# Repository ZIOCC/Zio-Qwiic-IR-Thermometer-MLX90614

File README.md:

# Zio Qwiic Surface IR Thermometer (MLX90614)

> This product can be available for purchase [here](https://www.smart-prototyping.com/Zio-Qwiic-Surface-Temperature-Infrared-Sensor-MLX9061).

##### Description

The latest incorporation to our Qwiic family is this high precision temperature module!  It has a very cool feature on sensing temperatures remotely thanks to the infrared light emitted. Most of the object temperature sensors need to be in contact to the object to take a measurement, but the ZIO IR Thermometer determines the light rebounding off objects, in this way the temperature can be sensed even if the object is located in a certain distance. To get a temperature measurement just point the sensor facing the object to evaluate and it will gather the data by absorbing the IR waves diffused.

The board incorporates an MLX90614 sensor, able to measure a wider range of temperatures than other temperature sensors - as it doesn’t need to make contact to the object’s surface. It can be used for many applications, it produces two temperature measurements. One for measuring the ambient temperature and another one to measure ambient temperature.  It measures temperature between -70 and 380°C (or -94 to 719.96 °F) for objects and -40 to 125 °C for ambient temperature.

It has a wide field-of-view angle: 90° - for every cm away from the object, the sensing area increases 2cm.

The sensor uses a 2-wire SMBus interface, with almost the same features as I2C. Actually, the MLX90614 has an I2C address (0x5A) which can be reconfigured. This is an awesome factor if you want to incorporate multiple MLX90614 at the same I2C bus to operate separately.

The multifunctional temperature sensor can also be read via PWM interface through the SDA (no need to use SCL, just use 3 wires for PWM interface). Getting data through PWM can be tricky on some occasions, but on the positive side, it is very powerful. We have also incorporated the sensor pinout at the board, by soldering the pin header provided the PWM interface can be easily used.

##### Specifications:

* Factory calibrated in wide temperature range:
    * -40 to 125  ̊C for sensor temperature and
    * -70 to 380  ̊C for object temperature.
* Resolution: 0.02°C
* Single and dual zone versions
* Current Consumption: 25mA
* Dimensions: 16.4 x 26.8mm
* Weight: 2.3g

##### Links

* [MLX90614 Datasheet](https://www.sparkfun.com/datasheets/Sensors/Temperature/MLX90614_rev001.pdf) 
* [Library link](https://github.com/adafruit/Adafruit-MLX90614-Library)

> ###### About Zio
> Zio is a new line of open sourced, compact, and grid layout boards, fully integrated for Arduino and Qwiic ecosystem. Designed ideally for wearables, robotics, small-space limitations or other on the go projects. Check out other awesome Zio products [here](https://www.smart-prototyping.com/Zio).

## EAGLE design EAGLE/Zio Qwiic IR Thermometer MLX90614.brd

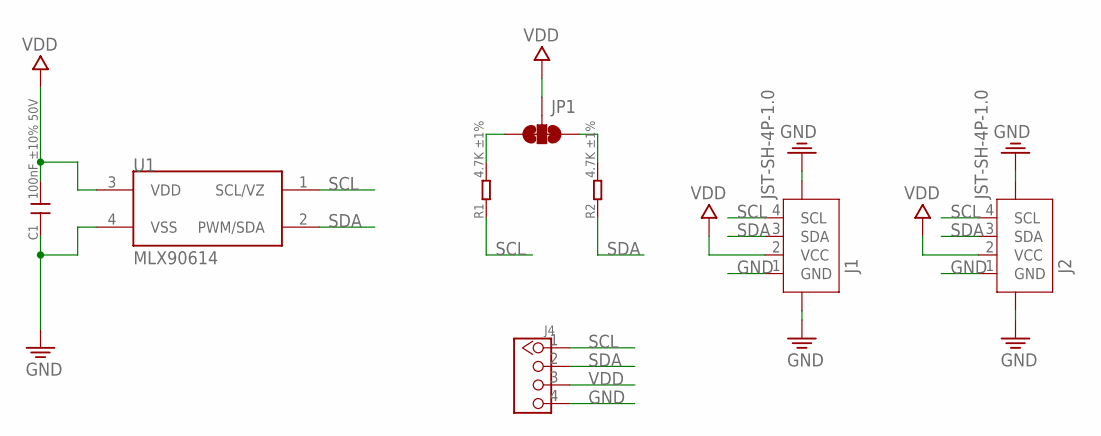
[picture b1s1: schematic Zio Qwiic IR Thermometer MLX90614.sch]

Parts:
C1: 100nF ±10% 50V; C0603
J1, J2: JST-SH-4P-1.0; JST-SH-4P
J4: HEADER-4P-60/35MIL; 4P-65/35MIL
JP1: SMT-JUMPER_3_2-NC_TRACE
R1, R2: 4.7K ±1%; R0603
U1: MLX90614; TO-39

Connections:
GND: C1.1, J1.1 (GND), J1.NC1 (5), J1.NC2 (6), J2.1 (GND), J2.NC1 (5), J2.NC2 (6), J4.4, U1.4 (VSS)
unnamed: JP1.3, R1.2
unnamed: JP1.1, R2.2
SCL: J1.4 (SCL), J2.4 (SCL), J4.1, R1.1, U1.1 (SCL/VZ)
SDA: J1.3 (SDA), J2.3 (SDA), J4.2, R2.1, U1.2 (PWM/SDA)
VDD: C1.2, J1.2 (VCC), J2.2 (VCC), J4.3, JP1.2, U1.3 (VDD)

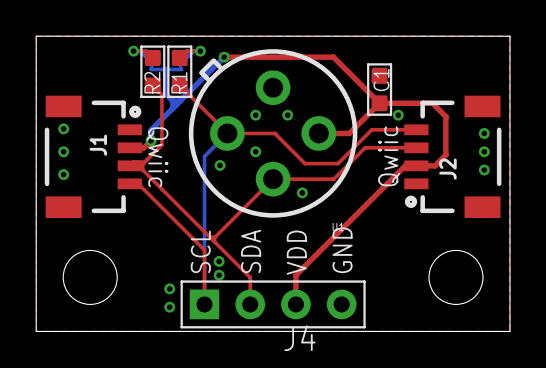
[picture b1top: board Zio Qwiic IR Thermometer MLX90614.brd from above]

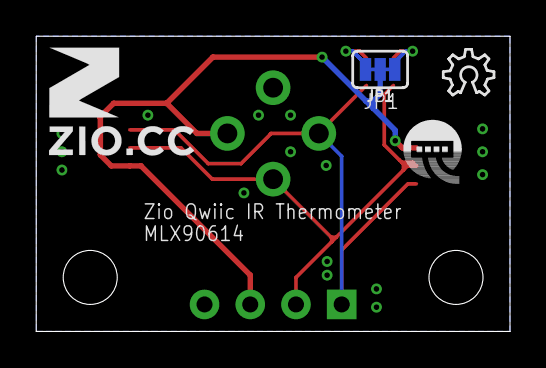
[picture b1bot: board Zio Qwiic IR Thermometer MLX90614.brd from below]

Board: 2 copper layers, 26.3 x 16.4 mm, 11 parts (4 on the bottom side), 6 nets.

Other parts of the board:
U$2: 6MM
U$3: OSHW_6X100_NOTEXT
U$4: QWIIC-LOGO-BASIC
